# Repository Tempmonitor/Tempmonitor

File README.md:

#Temp monitor
Temp monitor is a device the monitors system resources. It connects to a computer with a micro usb cable and a host program written in C# collects and sends system information to the device. 

The device is equiped with four 3 character 8-segments led displays. The device is controlled by a ATiny45 running the V-USB library to create create a HID USB device. 

More information about hardware, firmware and host softwar can be found in the subfolders of the repository.

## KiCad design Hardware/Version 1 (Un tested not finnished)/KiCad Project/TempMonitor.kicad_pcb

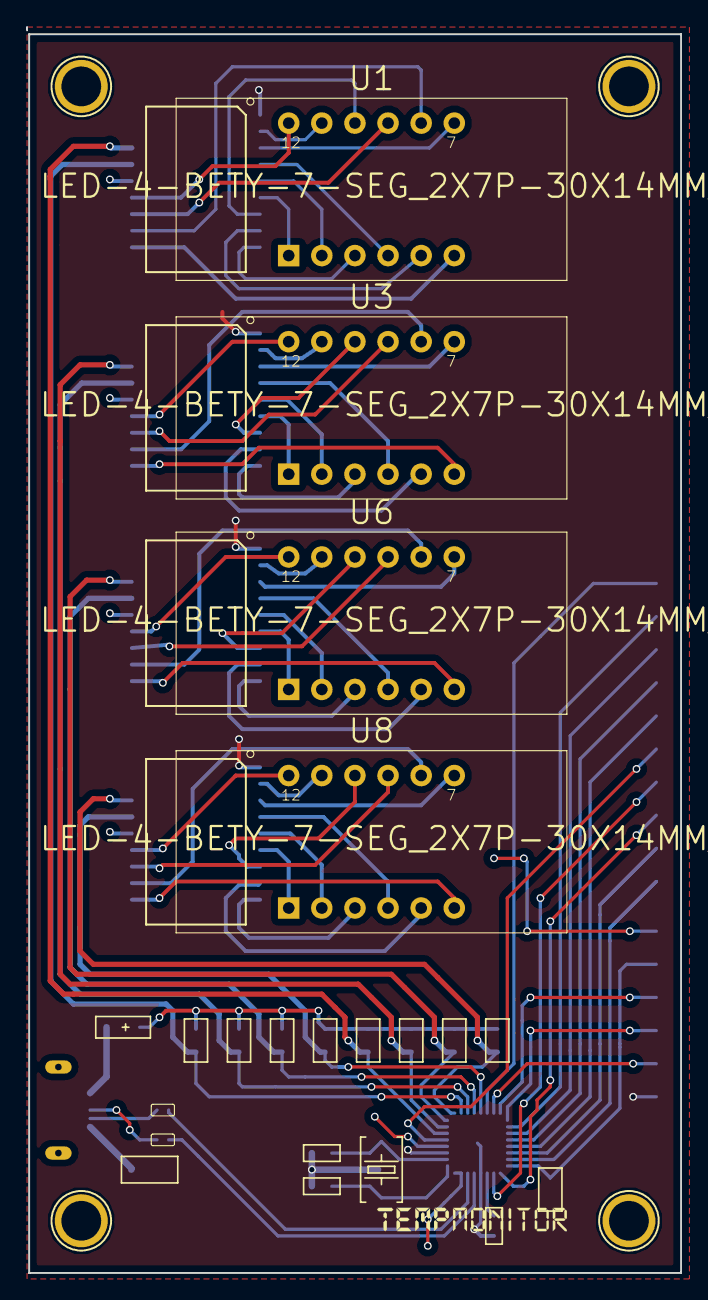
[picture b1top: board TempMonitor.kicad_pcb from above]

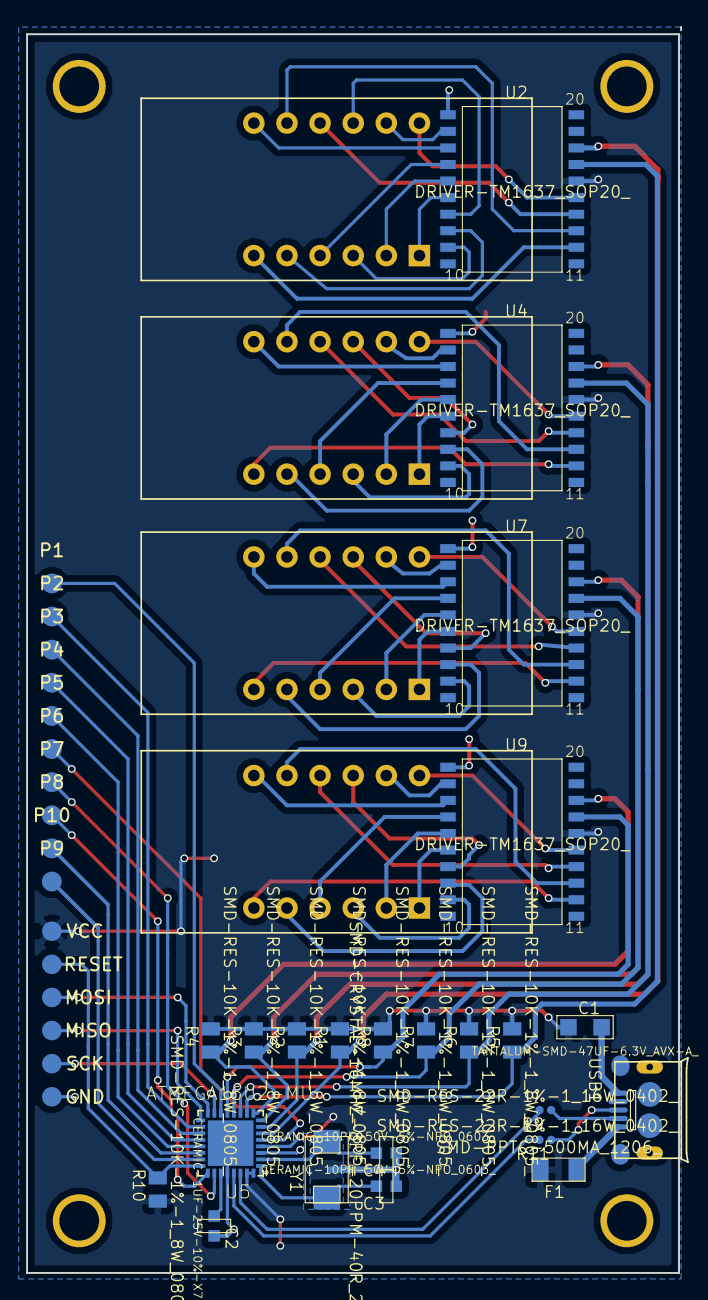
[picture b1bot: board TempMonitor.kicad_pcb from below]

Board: 2 copper layers, 50.2 x 95.6 mm, 38 parts (33 on the bottom side), 83 nets.

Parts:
C1: TANTALUM-SMD-47UF-6.3V_AVX-A_; AVX-A
C2: CERAMIC-1UF-25V-10%-X7R_0603_; C0603
C3, C4: CERAMIC-10PF-50V-5%-NPO_0603_; C0603
F1: SMD-PPTC-500MA_1206_; F1206
P1, P2, P3, P4, P5, P6, P7, P8, P9, P10: Pad
P11: ProgrammingPad
R1, R2, R3, R4, R5, R6, R7, R8, R10: SMD-RES-10K-1%-1_8W_0805_; R0805
R9, R11: SMD-RES-22R-1%-1_16W_0402_; R0402
U1, U3, U6, U8: LED-4-BETY-7-SEG_2X7P-30X14MM_; LCD12-2.54-30.0X14.0X7.3MM
U2, U4, U7, U9: DRIVER-TM1637_SOP20_; SOP20-1.27-12.7X7.65MM
U5: ATMEGA16U2-MU; QFN50P500X500X100-33N
USB1: MICRO-USB-SMD-B-_10118193-0001LF_; MICRO-USB5+6P-SMD-0.65-B_NY
Y1: SMD-CRYSTAL-16MHZ-8PF-20PPM-40R_2P-5.0X3.2MM_; X2-SMD-5.0X3.2X1.3MM

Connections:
A1: U1.11, U2.2
A2: U3.11, U4.2
A3: U6.11, U7.2
A4: U8.11, U9.2
B1: U1.7, U2.3
B2: U3.7, U4.3
B3: U6.7, U7.3
B4: U8.7, U9.3
C1: U1.4, U2.4
C2: U3.4, U4.4
C3: U6.4, U7.4
C4: U8.4, U9.4
CLK1: R1.1, U2.18, U5.6
CLK2: R2.1, U4.18, U5.7
CLK3: R3.1, U5.8, U7.18
CLK4: R4.1, U5.9, U9.18
D1: U1.2, U2.5
D2: U3.2, U4.5
D3: U6.2, U7.5
D4: U8.2, U9.5
D+: R11.1, USB1.3
D-: R9.1, USB1.2
DATA1: R5.1, U2.17, U5.10
DATA2: R6.1, U4.17, U5.11
DATA3: R7.1, U5.12, U7.17
DATA4: R8.1, U5.13, U9.17
DP1: U1.3, U2.9
DP2: U3.3, U4.9
DP3: U6.3, U7.9
DP4: U8.3, U9.9
E1: U1.1, U2.6
E2: U3.1, U4.6
E3: U6.1, U7.6
E4: U8.1, U9.6
F1: U1.10, U2.7
F2: U3.10, U4.7
F3: U6.10, U7.7
F4: U8.10, U9.7
G1: U1.5, U2.8
G2: U3.5, U4.8
G3: U6.5, U7.8
G4: U8.5, U9.8
GND: C2.2, C3.1, C4.1, P11.6, U2.1, U4.1, U5.3, U5.28, U5.33, U7.1, U9.1
GR11: U1.12, U2.15
GR12: U3.12, U4.15
GR13: U6.12, U7.15
GR14: U8.12, U9.15
GR21: U1.9, U2.14
GR22: U3.9, U4.14
GR23: U6.9, U7.14
GR24: U8.9, U9.14
GR31: U1.8, U2.13
GR32: U3.8, U4.13
GR33: U6.8, U7.13
GR34: U8.8, U9.13
GR41: U1.6, U2.12
GR42: U3.6, U4.12
GR43: U6.6, U7.12
GR44: U8.6, U9.12
MISO: P11.4, U5.17
MOSI: P11.3, U5.16
unnamed: C1.-, USB1.5
unnamed: C2.1, U5.27
unnamed: C3.2, U5.1, Y1.1
unnamed: C4.2, U5.2, Y1.2
unnamed: F1.1, USB1.1
unnamed: P1.1, U5.14
unnamed: P2.1, U5.18
unnamed: P3.1, U5.19
unnamed: P4.1, U5.20
unnamed: P5.1, U5.21
unnamed: P6.1, U5.5
unnamed: P7.1, U5.26
unnamed: P8.1, U5.25
unnamed: P9.1, U5.23
unnamed: P10.1, U5.22
unnamed: R9.2, U5.30
unnamed: R11.2, U5.29
unnamed: USB1.S3, USB1.S4
unnamed: USB1.S5, USB1.S6
RESET: P11.2, R10.2, U5.24
SCK: P11.5, U5.15
VCC: C1.+, F1.2, P11.1, R1.2, R2.2, R3.2, R4.2, R5.2, R6.2, R7.2, R8.2, R10.1, U2.16, U4.16, U5.4, U5.31, U5.32, U7.16, U9.16

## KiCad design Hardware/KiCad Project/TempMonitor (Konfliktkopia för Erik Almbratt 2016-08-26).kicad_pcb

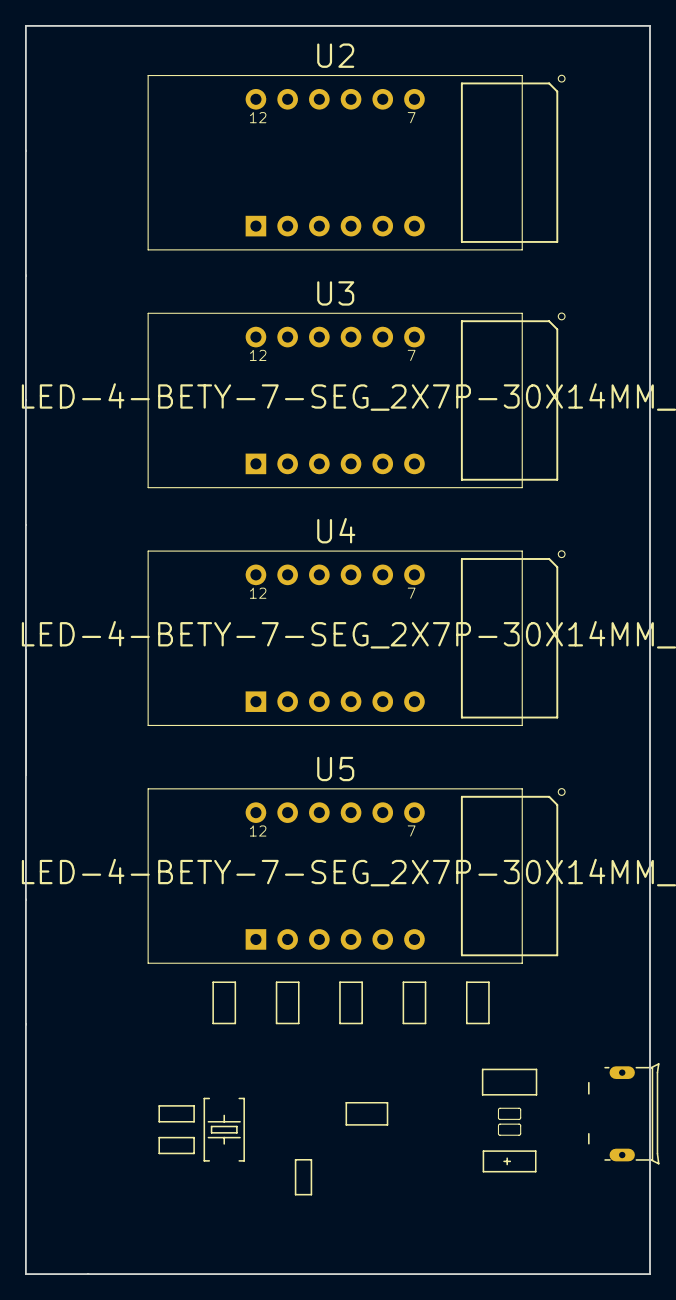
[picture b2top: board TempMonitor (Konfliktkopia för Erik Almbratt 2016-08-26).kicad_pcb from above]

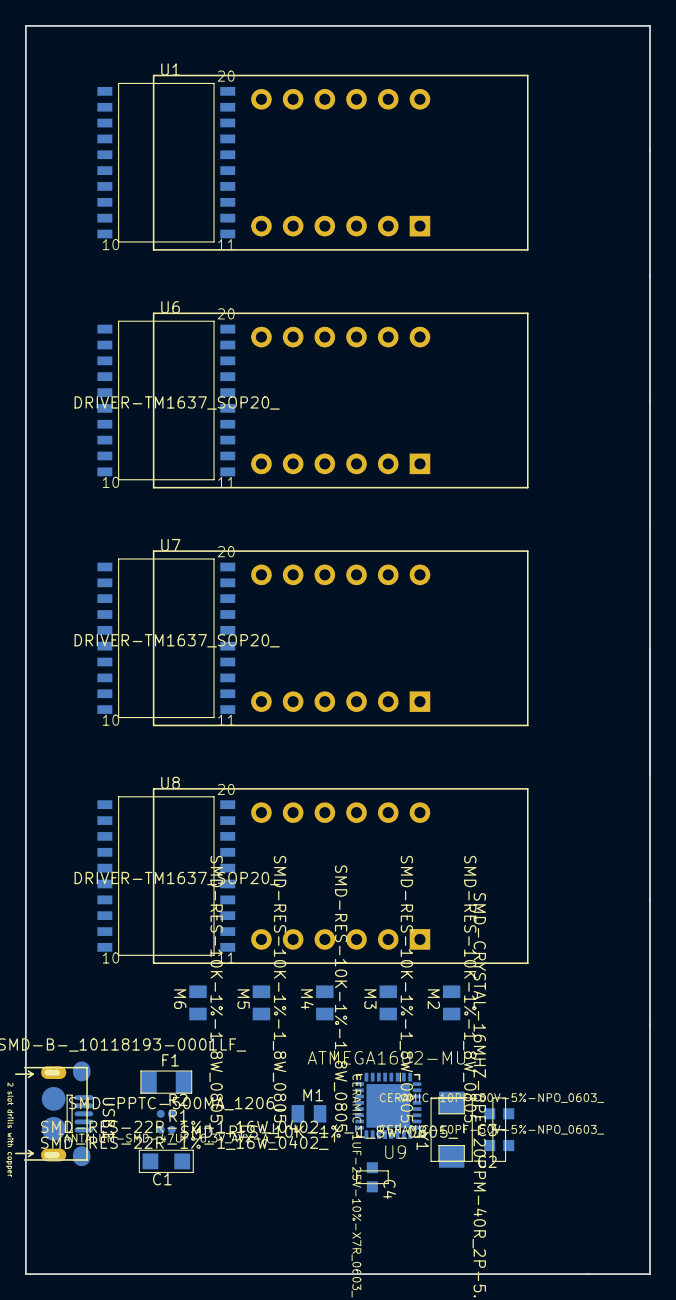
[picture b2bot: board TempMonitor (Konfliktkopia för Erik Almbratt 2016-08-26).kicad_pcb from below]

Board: 2 copper layers, 50.0 x 100.0 mm, 24 parts (20 on the bottom side), 66 nets, no tracks yet.

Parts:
C1: TANTALUM-SMD-47UF-6.3V_AVX-A_; AVX-A
C2, C3: CERAMIC-10PF-50V-5%-NPO_0603_; C0603
C4: CERAMIC-1UF-25V-10%-X7R_0603_; C0603
F1: SMD-PPTC-500MA_1206_; F1206
M1, M2, M3, M4, M5, M6: SMD-RES-10K-1%-1_8W_0805_; R0805
R1, R2: SMD-RES-22R-1%-1_16W_0402_; R0402
U1, U6, U7, U8: DRIVER-TM1637_SOP20_; SOP20-1.27-12.7X7.65MM
U2, U3, U4, U5: LED-4-BETY-7-SEG_2X7P-30X14MM_; LCD12-2.54-30.0X14.0X7.3MM
U9: ATMEGA16U2-MU; QFN50P500X500X100-33N
USB1: MICRO-USB-SMD-B-_10118193-0001LF_; MICRO-USB5+6P-SMD-0.65-B
Y1: SMD-CRYSTAL-16MHZ-8PF-20PPM-40R_2P-5.0X3.2MM_; X2-SMD-5.0X3.2X1.3MM

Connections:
A1: U1.2, U2.11
A2: U3.11, U6.2
A3: U4.11, U7.2
A4: U5.11, U8.2
B1: U1.3, U2.7
B2: U3.7, U6.3
B3: U4.7, U7.3
B4: U5.7, U8.3
C1: U1.4, U2.4
C2: U3.4, U6.4
C3: U4.4, U7.4
C4: U5.4, U8.4
CLK: M2.1, U1.18, U6.18, U7.18, U8.18, U9.6
D1: U1.5, U2.2
D2: U3.2, U6.5
D3: U4.2, U7.5
D4: U5.2, U8.5
D+: R1.1, USB1.3
D-: R2.1, USB1.2
DATA1: M3.1, U1.17, U9.7
DATA2: M4.1, U6.17, U9.8
DATA3: M5.1, U7.17, U9.9
DATA4: M6.1, U8.17, U9.10
DP1: U1.9, U2.3
DP2: U3.3, U6.9
DP3: U4.3, U7.9
DP4: U5.3, U8.9
E1: U1.6, U2.1
E2: U3.1, U6.6
E3: U4.1, U7.6
E4: U5.1, U8.6
F1: U1.7, U2.10
F2: U3.10, U6.7
F3: U4.10, U7.7
F4: U5.10, U8.7
G1: U1.8, U2.5
G2: U3.5, U6.8
G3: U4.5, U7.8
G4: U5.5, U8.8
GND: C1.-, C2.1, C3.1, C4.2, U1.1, U6.1, U7.1, U8.1, U9.3, U9.28, U9.33, USB1.5
GR11: U1.15, U2.12
GR12: U3.12, U6.15
GR13: U4.12, U7.15
GR14: U5.12, U8.15
GR21: U1.14, U2.9
GR22: U3.9, U6.14
GR23: U4.9, U7.14
GR24: U5.9, U8.14
GR31: U1.13, U2.8
GR32: U3.8, U6.13
GR33: U4.8, U7.13
GR34: U5.8, U8.13
GR41: U1.12, U2.6
GR42: U3.6, U6.12
GR43: U4.6, U7.12
GR44: U5.6, U8.12
unnamed: C2.2, U9.1, Y1.1
unnamed: C3.2, U9.2, Y1.2
unnamed: C4.1, U9.27
unnamed: F1.1, USB1.1
unnamed: R1.2, U9.29
unnamed: R2.2, U9.30
unnamed: USB1.S3, USB1.S4
unnamed: USB1.S5, USB1.S6
RESET: M1.2, U9.24
VCC: C1.+, F1.2, M1.1, M2.2, M3.2, M4.2, M5.2, M6.2, U1.16, U6.16, U7.16, U8.16, U9.4, U9.31, U9.32

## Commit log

2016-09-06 Initial hardware
    PCBnew not complete.
2016-09-17 Basic interface (Dummy)
2016-09-17 Design + added ballonTip
2016-09-18 Writes and loads user settings
2016-09-18 Removed unused array
2016-09-18 Added inno setup
2016-09-18 32-bit compile
2016-09-18 Fix elevated user promt
2016-09-18 Added library and licenses
2016-09-22 Update
    Gerber files added, BOM added, PCB redone, separate clock traces for
    led-drivers made.
2016-09-23 Update
    Logo exchanged, gerbers updated and BOM updated and redone, now with MPN
    instead of Seeed SKU.
2016-09-23 Hotfix
    Values not included in gerber.
2016-10-05 Added inital new pcb version
2016-10-06 Firmware base framework
2016-10-19 PCB layout
    PCB routed, need of silkscreen fixes. Directory clean up.
2016-10-20 Added loggos
2016-10-23 USB circuit fix
    USB circuit fix R3 incorrectly connected. Added filtering capacitors to MCU and shift registers. Centered displays.
2016-10-23 Fix LED display wiring
2016-10-25 PCB fix
    Removed C6 value+ more space for R3, R1 & D1
2016-10-27 Hotfix
    Unnecessary front silkscreen removed, some silkscreen moved from front
    to back and silkscreen references moved.
2016-11-23 Version 1.0
2016-11-23 Gerber files Version 1.0
2016-11-23 Fix corrupted file
2016-12-15 Update Added codeblocks project, license-, display- and shift register files.
2016-12-15 removed binaries
2016-12-15 Added resource directory
2016-12-15 Fixed typo
2016-12-15 Updated files in project
2016-12-18 Added HidLibrary
2016-12-18 License update
2016-12-19 Moved files
2016-12-19 Added host files
2016-12-19 Added main licens and readme
2016-12-19 Added schematic in PDF
2016-12-20 Typo
2016-12-22 Revert "Hotfix"
    This reverts commit b01ab2ca72f5422068492f297ba1483d4015dfa4.
2016-12-23 Various updates Automatic oscillator calibration, display driver
2017-01-07 Comments added and timer routine cleanup
2017-01-08 Cleanup
2017-01-09 Faster shiftout Increased transfer speed
2017-01-09 Device connection made and label change added
2017-01-09 HID reconnection added
2017-01-10 Minor cleanup
2017-01-10 Test output and slider added
2017-01-10 USB Config update Updated VID, PID, vendor name and device name
2017-01-10 Updated display function Remove 0 before number
2017-01-11 Outputdata function started
2017-01-11 Changed icons
2017-01-11 Compiled test installationfile
2017-01-11 Output and UI value working
2017-01-11 Minor fix
    Changed Display 2 Combobox to correct style.
2017-01-11 Return GPU load and temperature fix
2017-01-12 Changed VID & PID, added battery info
2017-01-14 Autostart
2017-01-14 Added license
2017-01-14 Esthetical fix
2017-01-14 Autorun as default, only show form first time
2017-01-14 Notifyicon shows status
2017-01-14 Changed assemblyname and removed notfication ballones
2017-02-02 Receive raw data from computer Instead of receiving digit numbers computer controls all the display segments
2017-02-02 Brightness control Using Timer1 compare match to control brightness of displays.
2017-02-02 Remove test project
2017-02-02 Removed unused controles
2017-02-18 Receive plain data, turn of display on low brightness
2017-02-18 Added brightness control
2017-02-19 Compiled installation file
2017-02-25 USB recive timout If no data have been received in a cirtain amount of time, turn of displays.
2017-02-26 Cleanup + through hole usb
2017-03-02 Moved shift registers Board is not completed
